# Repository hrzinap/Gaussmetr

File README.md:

# Gaussmetr
## Elixír do škol 2026
Archiv obsahuje potřebné soubory pro výrobu jednoduchého magnetometru (využívajícího Hallův senzor)
Jsou zde dostupné zdrojové kódy desky pro případné zpracování výrobních podkladů (formát KiCad 10)
Je použit klon desky Arduino NANO s procesorem Čínské výroby [LGT8f328p](https://wolles-elektronikkiste.de/lgt8f328p-lqfp32-boards).
K tomuto klonu je nutné stáhnout do vývojového prostředí Arduino IDE definici desky a základních knihoven.
[Více GitHub](https://github.com/dbuezas/lgt8fx)
Použití tohto procesoru umožní využít kombinace D/A a A/D převodníku pro kompenzaci ofsetu Hallova čidla. 
Navrženou desku plošných spojů lze použít i pro běžné Arduino NANO, ale je nutná úprava řídicího SW a bez dalších HW úprav se bude obtížně dosahovat symetrie měření. Nic méně sestava bude pro demonstrační účely použitelná.

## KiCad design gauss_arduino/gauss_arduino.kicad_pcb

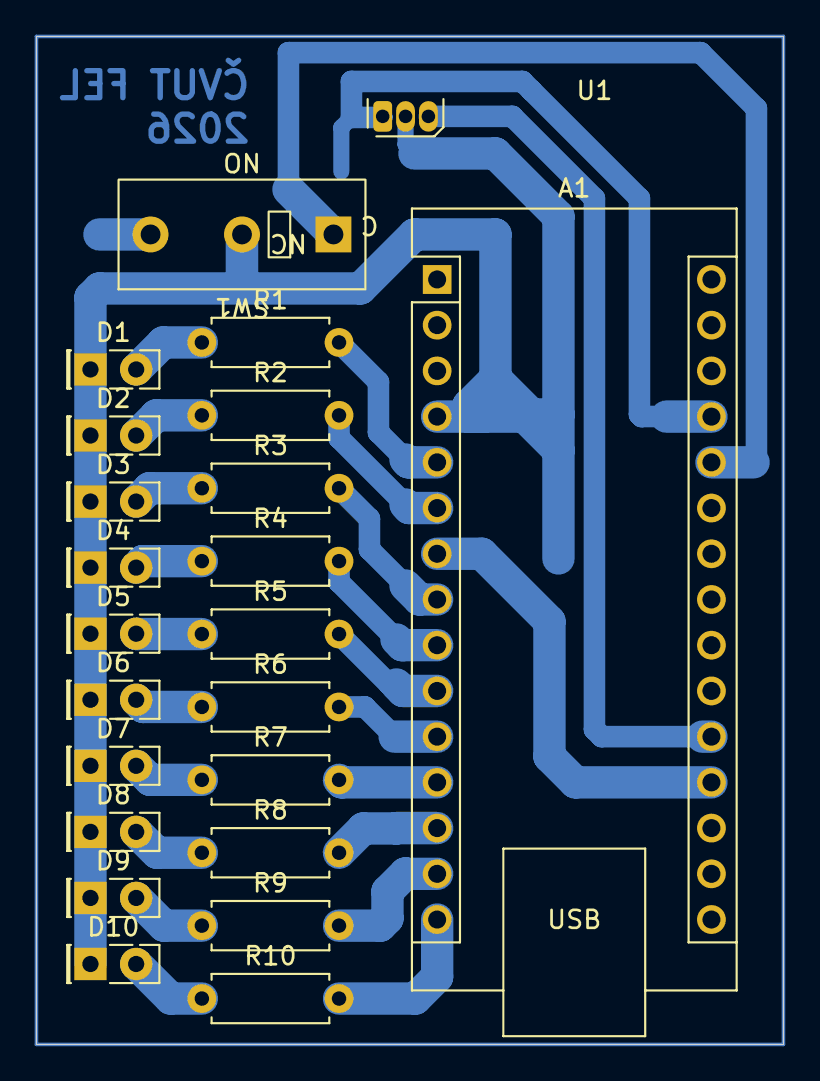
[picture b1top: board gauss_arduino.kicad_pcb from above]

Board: 2 copper layers, 41.5 x 56.0 mm, 24 parts (1 on the bottom side), 25 nets.

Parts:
A1: Arduino_LGT8F328P; Arduino_Nano
C1: 100nF; C_1206_3216Metric_Pad1.33x1.80mm_HandSolder
D1, D2, D3, D4: Č; LED_Rectangular_W5.0mm_H2.0mm
D5, D6: Ž; LED_Rectangular_W5.0mm_H2.0mm
D7, D8, D9, D10: Z; LED_Rectangular_W5.0mm_H2.0mm
R1: 10x 510R; R_Axial_DIN0207_L6.3mm_D2.5mm_P7.62mm_Horizontal
R2, R3, R4, R5, R6, R7, R8, R9, R10: R_Axial_DIN0207_L6.3mm_D2.5mm_P7.62mm_Horizontal
SW1: SW_XKB_DM1-16UP-1
U1: Mag. senzor; TO-92S

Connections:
unnamed: A1.27 (+5V), C1.1, U1.1 (V_{CC})
unnamed: A1.7 (D4), A1.19 (A0)
unnamed: A1.20 (A1), U1.3 (V_{OUT})
unnamed: A1.26 (A7), SW1.1 (A)
unnamed: A1.5 (D2), R1.2
unnamed: A1.6 (D3), R2.2
unnamed: A1.8 (D5), R3.2
unnamed: A1.9 (D6), R4.2
unnamed: A1.10 (D7), R5.2
unnamed: A1.11 (D8), R6.2
unnamed: A1.12 (D9), R7.2
unnamed: A1.13 (D10), R8.2
unnamed: A1.14 (D11), R9.2
unnamed: A1.15 (D12), R10.2
unnamed: D1.2 (A), R1.1
unnamed: A1.4 (GND), C1.2, D1.1 (K), D2.1 (K), D3.1 (K), D4.1 (K), D5.1 (K), D6.1 (K), D7.1 (K), D8.1 (K), D9.1 (K), D10.1 (K), SW1.2 (B), U1.2 (GND)
unnamed: D2.2 (A), R2.1
unnamed: D3.2 (A), R3.1
unnamed: D4.2 (A), R4.1
unnamed: D5.2 (A), R5.1
unnamed: D6.2 (A), R6.1
unnamed: D7.2 (A), R7.1
unnamed: D8.2 (A), R8.1
unnamed: D9.2 (A), R9.1
unnamed: D10.2 (A), R10.1
